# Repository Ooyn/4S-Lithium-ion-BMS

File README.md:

# 4S-Lithium-ion-BMS
This repository contains the schematic and design files for a custom 4S Lithium-ion Battery Management System (BMS). Utilizing an active shunt architecture, this project is designed to safely charge and balance a four-cell series battery pack. The system features a primary power input stage protected against reverse polarity by a MOSFET, followed by an LM317 adjustable linear voltage regulator. This regulator, paired with a potentiometer and filtering capacitors, allows for precise tuning of the total pack charging voltage, typically targeted at 16.8V.

The core of the balancing circuitry consists of four identical active shunt modules, with one dedicated to monitoring each individual cell. Each module employs a TL431LP precision voltage reference, configured with a resistor divider network. This setup allows the TL431LP to act as a highly accurate analog comparator, continuously monitoring the specific voltage of its connected cell as the entire battery pack charges.

As the voltage across an individual cell rises and hits the critical 4.2V maximum threshold, its corresponding TL431LP begins to conduct. This conduction pulls current from the base of a paired BD140 PNP power transistor, activating it to open a parallel bypass path. Consequently, the charging current is successfully routed around the fully charged cell and safely dissipated as heat through a series array of 1N4007 diodes.

Dedicated LEDs on each module provide immediate visual feedback when this bypass circuit is active. By seamlessly shunting current away from fully charged cells, this custom BMS prevents overvoltage degradation while maintaining the continuous series charging loop. This mechanism ensures that any remaining under-charged cells can safely reach their maximum capacity without risking damage to the rest of the pack.

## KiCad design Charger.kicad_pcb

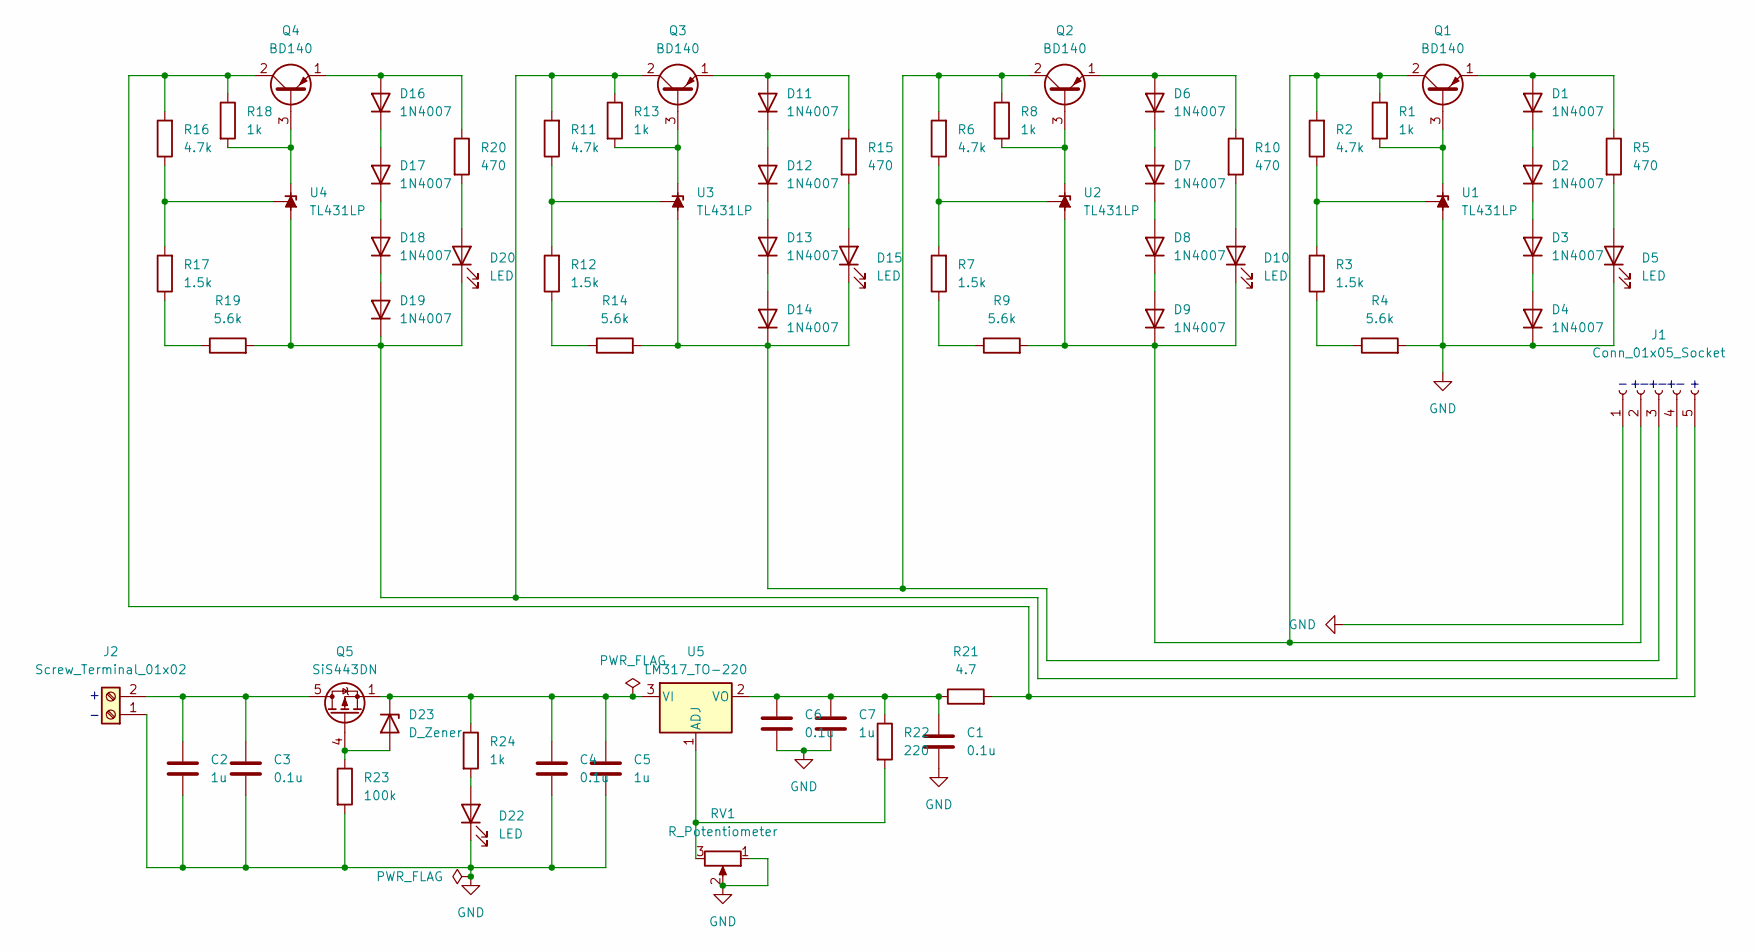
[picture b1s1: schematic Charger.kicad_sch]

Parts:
C1: 0.1u; C_Disc_D7.5mm_W2.5mm_P5.00mm
C2, C5, C7: 1u; C_Disc_D5.0mm_W2.5mm_P5.00mm
C3, C4, C6: 0.1u; C_Disc_D5.0mm_W2.5mm_P5.00mm
D1, D2, D3, D4, D6, D7, D8, D9, D11, D12, D13, D14, D16, D17, D18, D19: 1N4007; D_DO-41_SOD81_P7.62mm_Horizontal
D5, D10, D15, D20, D22: LED; LED_D3.0mm_Clear
D23: D_Zener; D_DO-35_SOD27_P7.62mm_Horizontal
J1: Conn_01x05_Socket; Molex_PicoBlade_53047-0510_1x05_P1.25mm_Vertical
J2: Screw_Terminal_01x02; TerminalBlock_Xinya_XY308-2.54-2P_1x02_P2.54mm_Horizontal
Q1, Q2, Q3, Q4: BD140; TO-126-3_Horizontal_TabDown
Q5: SiS443DN; Vishay_PowerPAK_1212-8_Single
R1, R8, R13, R18, R24: 1k; R_Axial_DIN0204_L3.6mm_D1.6mm_P5.08mm_Horizontal
R2, R6, R11, R16: 4.7k; R_Axial_DIN0204_L3.6mm_D1.6mm_P5.08mm_Horizontal
R3, R7, R12, R17: 1.5k; R_Axial_DIN0204_L3.6mm_D1.6mm_P5.08mm_Horizontal
R4, R9, R14, R19: 5.6k; R_Axial_DIN0204_L3.6mm_D1.6mm_P5.08mm_Horizontal
R5, R10, R15, R20: 470; R_Axial_DIN0204_L3.6mm_D1.6mm_P5.08mm_Horizontal
R21: 4.7; R_Axial_DIN0204_L3.6mm_D1.6mm_P5.08mm_Horizontal
R22: 220; R_Axial_DIN0204_L3.6mm_D1.6mm_P5.08mm_Horizontal
R23: 100k; R_Axial_DIN0204_L3.6mm_D1.6mm_P5.08mm_Horizontal
RV1: R_Potentiometer; Potentiometer_Bourns_3296W_Vertical
U1, U2, U3, U4: TL431LP; TO-92L_HandSolder
U5: LM317_TO-220; TO-220-3_Horizontal_TabDown

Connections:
GND: C1.2, C2.2, C3.2, C4.1, C5.1, C6.1, C7.1, D4.1 (K), D5.1 (K), D22.1 (K), J1.1, J2.1, R4.2, R23.2, RV1.1, RV1.2, U1.2 (A)
unnamed: D1.2 (A), Q1.1 (E), R5.1
unnamed: D1.1 (K), D2.2 (A)
unnamed: D2.1 (K), D3.2 (A)
unnamed: D3.1 (K), D4.2 (A)
unnamed: D5.2 (A), R5.2
unnamed: D6.2 (A), Q2.1 (E), R10.1
unnamed: D6.1 (K), D7.2 (A)
unnamed: D7.1 (K), D8.2 (A)
unnamed: D8.1 (K), D9.2 (A)
unnamed: D10.2 (A), R10.2
unnamed: D9.1 (K), D10.1 (K), J1.2, Q1.2 (C), R1.1, R2.2, R9.2, U2.2 (A)
unnamed: D11.2 (A), Q3.1 (E), R15.1
unnamed: D11.1 (K), D12.2 (A)
unnamed: D12.1 (K), D13.2 (A)
unnamed: D13.1 (K), D14.2 (A)
unnamed: D14.1 (K), D15.1 (K), J1.3, Q2.2 (C), R6.2, R8.1, R14.2, U3.2 (A)
unnamed: D15.2 (A), R15.2
unnamed: D16.2 (A), Q4.1 (E), R20.1
unnamed: D16.1 (K), D17.2 (A)
unnamed: D17.1 (K), D18.2 (A)
unnamed: D18.1 (K), D19.2 (A)
unnamed: D19.1 (K), D20.1 (K), J1.4, Q3.2 (C), R11.2, R13.1, R19.2, U4.2 (A)
unnamed: D20.2 (A), R20.2
unnamed: D22.2 (A), R24.2
unnamed: D23.2 (A), Q5.4 (G), R23.1
unnamed: C4.2, C5.2, D23.1 (K), Q5.1 (S), Q5.2 (S), Q5.3 (S), R24.1, U5.3 (VI)
unnamed: J1.5, Q4.2 (C), R16.2, R18.1, R21.2
unnamed: C2.1, C3.1, J2.2, Q5.5 (D)
unnamed: Q1.3 (B), R1.2, U1.3 (K)
unnamed: Q2.3 (B), R8.2, U2.3 (K)
unnamed: Q3.3 (B), R13.2, U3.3 (K)
unnamed: Q4.3 (B), R18.2, U4.3 (K)
unnamed: R3.1, R4.1
unnamed: R7.1, R9.1
unnamed: R12.1, R14.1
unnamed: R17.1, R19.1
unnamed: R2.1, R3.2, U1.1 (REF)
unnamed: R6.1, R7.2, U2.1 (REF)
unnamed: R11.1, R12.2, U3.1 (REF)
unnamed: R16.1, R17.2, U4.1 (REF)
unnamed: R22.2, RV1.3, U5.1 (ADJ)
unnamed: C1.1, C6.2, C7.2, R21.1, R22.1, U5.2 (VO)

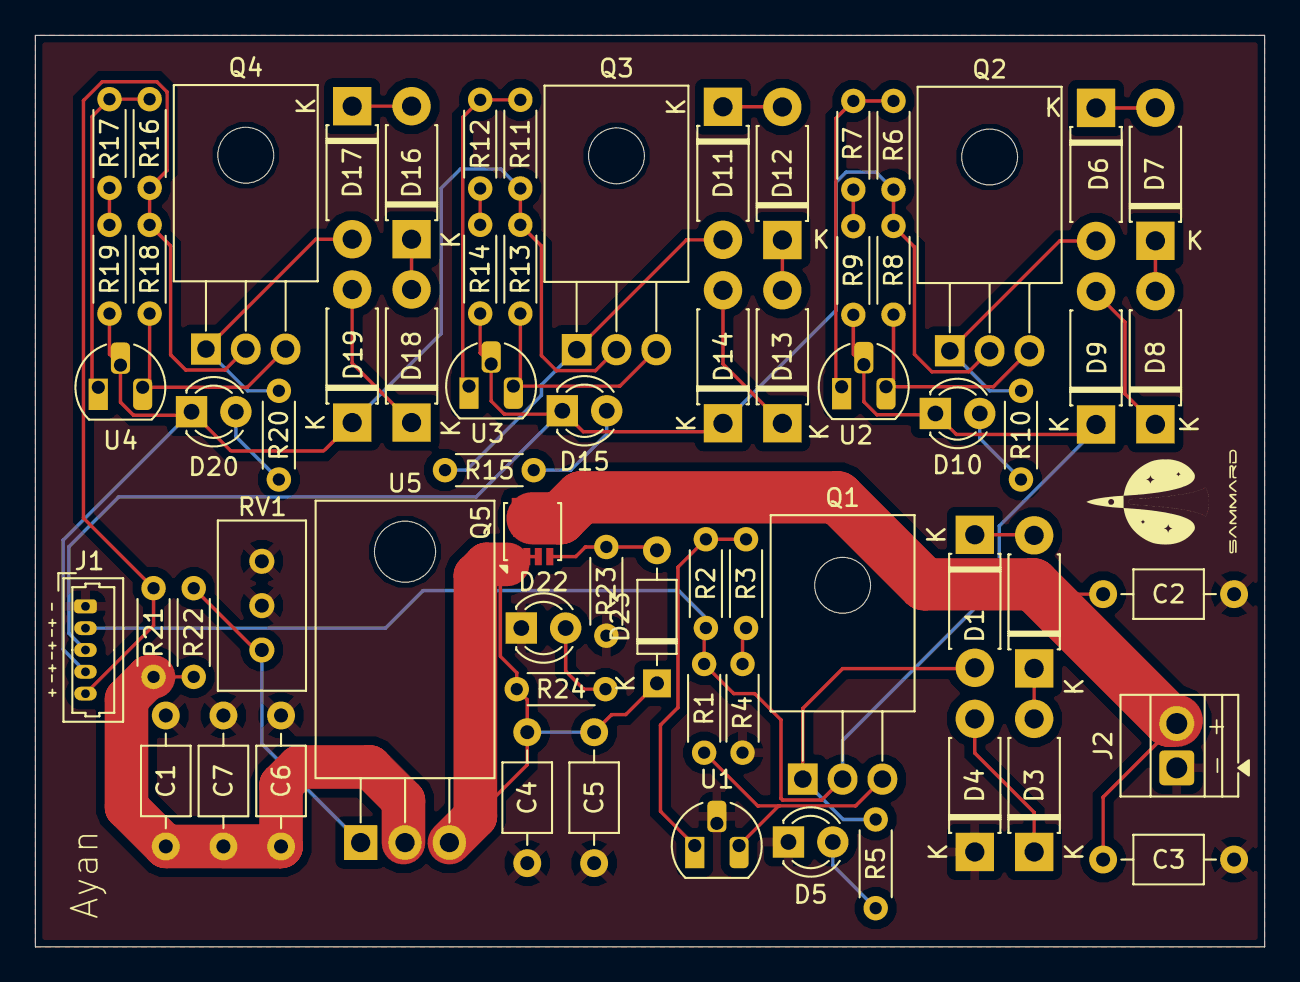
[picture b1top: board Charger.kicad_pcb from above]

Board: 2 copper layers, 70.4 x 52.2 mm, 66 parts (0 on the bottom side), 43 nets.

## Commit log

2026-03-11 Create LICENSE
